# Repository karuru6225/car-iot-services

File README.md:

# car-iot-services

車載 IoT システム。ESP32-S3 が車載バッテリー電圧・電流・電力を計測し、
SORACOM Cat-M 経由で AWS IoT Core に送信する。
クラウド側では S3 + Athena でデータを蓄積し、CloudFront ホスティングの Web 管理画面でグラフ表示・削除操作を行える。

## システム構成

```text
ESP32-S3-MINI-1 (esp32_iot_gateway)
  ├── ADS1115 で 2 系統バッテリー電圧測定（サブ / メイン）
  ├── INA228 でサブバッテリー電流・電力・温度測定
  └── BLE スキャンで SwitchBot センサー（温湿度計 / CO2）受信
        ↓ MQTT over TLS
  SIM7080G (SORACOM Cat-M)
        ↓
  AWS IoT Core
  ├── Topic Rule → Lambda (ingest) → S3 (raw/year=.../month=.../day=.../hour=.../)
  │                                         ↓ Glue + Athena
  │                                   API Gateway → Lambda (query / delete)
  │                                         ↑ CloudFront → Web 管理画面 (index.html)
  ├── Shadow (desired/delta) → デバイス設定変更（充電制御・閾値等）
  └── IoT Jobs → OTA ファームウェア更新

  ※ 上記の LTE 経路とは別に、車内では BLE でスマートフォンと直接つながる
ESP32-S3-MINI-1 (esp32_iot_gateway)
        ↓ BLE (GATT Notify: 計測値・OBD-II)
  Android アプリ (car_iot_android)
    ├── Foreground Service で接続維持（アプリを閉じても受信継続）
    ├── Room に蓄積 → API Gateway へバッチアップロード（Cognito 認証）
    └── バッテリー / OBD / メーター表示・PiP
```

## ハードウェア

| 項目 | 内容 |
| ---- | ---- |
| MCU | ESP32-S3-MINI-1-N8（`m5atom_power_adc` 基板直付け） |
| ADC | ADS1115（I2C: SDA=GPIO17, SCL=GPIO18, ADDR=0x48） |
| 電流計 | INA228（I2C: SDA=GPIO17, SCL=GPIO18, ADDR=0x40） |
| OLED | SSD1306 128×64（I2C: SDA=GPIO17, SCL=GPIO18, ADDR=0x3C） |
| BLE | SwitchBot WoIOSensor（温湿度計）/ CO2センサー（アドバタイズ受信） |
| ボタン | GPIO26（Btn0）/ GPIO33（Btn1） |
| LTE | M5Stack U128（SIM7080G CAT-M/NB-IoT）、SORACOM SIM |
| 電源 | 車載 12V → LM2596（12V→5V）→ AMS1117-3.3（5V→3.3V）→ ESP32 |

## リポジトリ構成

```text
car-iot-services/
├── esp32_iot_gateway/     ESP32-S3-MINI-1 ゲートウェイ（アクティブ）
│   ├── ARCHITECTURE.md    レイヤー構成・依存ルール
│   ├── CONTEXT.md         実装詳細・設計決定・TODO
│   ├── OTA.md             OTA 仕様
│   ├── RELEASE.md         リリース手順（GitHub Actions）
│   └── MENU.md            OLED メニュー仕様
├── m5atom_iot_gateway/    M5Atom S3 ゲートウェイ（段階的廃止予定）
├── car_iot_android/       Android アプリ（Kotlin + Jetpack Compose、BLE 受信・アップロード）
│   └── CONTEXT.md         実装状態・実機検証メモ・UIデザインの設計判断
├── m5atom_power_adc/      新 PCB KiCad プロジェクト（電源・ADC・リレー・ESP32-S3 直付け）
│   ├── HARDWARE.md        ハードウェア設計仕様（BOM・回路・PCB レイアウト）
│   ├── CIRCUIT.md         回路設計仕様書
│   └── *.kicad_sch        階層シート構成（メイン + GroveUnit / RelayControl / VoltageSense）
├── infra/                 クラウドインフラ（Terraform）
│   ├── manage.ps1         デプロイスクリプト（plan / apply）
│   └── lambda_src/        Lambda ソースコード
│       └── TESTING.md     Lambdaユニットテストの実行方法（Docker + moto + pytest）
├── ops/                   運用スクリプト
│   ├── provision_device.ps1  ESP32 初回プロビジョニング（証明書発行・SPIFFS 書き込み）
│   ├── gen_certs.ps1      証明書生成
│   └── send_command.ps1   IoT Jobs コマンド送信
├── web/
│   ├── index.html         Web 管理画面（グラフ表示・データ削除）
│   └── admin.html         管理画面（デバイス一覧・Shadow 設定・充電制御）
├── docs/                  調査・設計メモ
├── tools/                 開発補助ツール（KiCad MCP サーバー等）
├── rtx830_filter_updater/ RTX830 フィルタ更新スクリプト
├── ARCHITECTURE.md
├── CONTEXT.md             開発引き継ぎ資料
└── SIM7080G.md            SIM7080G AT コマンドリファレンス
```

## デプロイ

### 前提

- Terraform >= 1.5
- AWS CLI（認証済み）
- 以下のファイルを `infra/` に配置（gitignore 済み）:
  - `backend.tfbackend` — S3 バックエンド設定
  - `terraform.tfvars` — 変数定義（`hosted_zone_id`, `web_subdomain` 等、`terraform.tfvars.example` を参照）

### インフラ + Lambda

`infra/` ディレクトリで PowerShell を実行:

```powershell
# 変更確認
.\manage.ps1 plan

# 適用（確認プロンプトあり）
.\manage.ps1 apply

# 確認なしで即適用
.\manage.ps1 apply -AutoApprove

# AWS プロファイルを指定する場合
.\manage.ps1 apply -Profile myprofile
```

Lambda コード（`lambda_src/`）の変更も `apply` で自動デプロイされる（`archive_file` の `source_code_hash` で変更検知）。

### Web 管理画面

`index.html` は `aws_s3_object` で Terraform 管理されているため、`manage.ps1 apply` で自動アップロードされる。
API エンドポイント・Cognito 設定はデプロイ時に Terraform が HTML 内のプレースホルダーを置換して埋め込む。

CloudFront のキャッシュ TTL はデフォルト 300 秒。URL は apply 後に確認できる:

```powershell
cd infra
terraform output web_url
```

## デバイスファームウェア

PlatformIO でビルド・書き込み。`esp32_iot_gateway/` を参照。

### 初回プロビジョニング

```powershell
cd ops
.\provision_device.ps1 -Port COM3
# AWS プロファイルを指定する場合
.\provision_device.ps1 -Port COM3 -Profile myprofile
# m5atom_power_adc v2 基板の場合（未指定時は v1 = 1）
.\provision_device.ps1 -Port COM3 -BoardVersion 2
```

スクリプトが MAC アドレスからデバイス ID（`esp32-gw-xxxxxxxxxxxx`）を生成し、AWS IoT Core に Thing を登録・証明書を発行・SPIFFS に書き込む。基板バージョンは NVS（`device/board_version`）にも書き込まれる。

同時に `-BoardVersion` に応じた Thing グループ（`ota-target-car-iot-gw-v1` または `-v2`）へも自動登録され、OTA の配信対象になる。グループに入っていないデバイスには OTA ジョブが届かない。

### OTA リリース

`vX.Y.Z` タグを push すると GitHub Actions が自動でビルド・S3 アップロード・IoT Job 作成・GitHub Release を実行する。MAJOR桁は基板シリーズ固定（1=v1基板、2=v2基板）。`src/config.h` の `FIRMWARE_VERSION_BASE` が正で、タグの数字と一致しないとビルドはエラーで停止する（先に `config.h` を更新してからタグを打つ）。

```powershell
git tag v1.2.3
git push origin main --tags
```

詳細は [esp32_iot_gateway/RELEASE.md](esp32_iot_gateway/RELEASE.md) および [esp32_iot_gateway/OTA.md](esp32_iot_gateway/OTA.md) を参照。

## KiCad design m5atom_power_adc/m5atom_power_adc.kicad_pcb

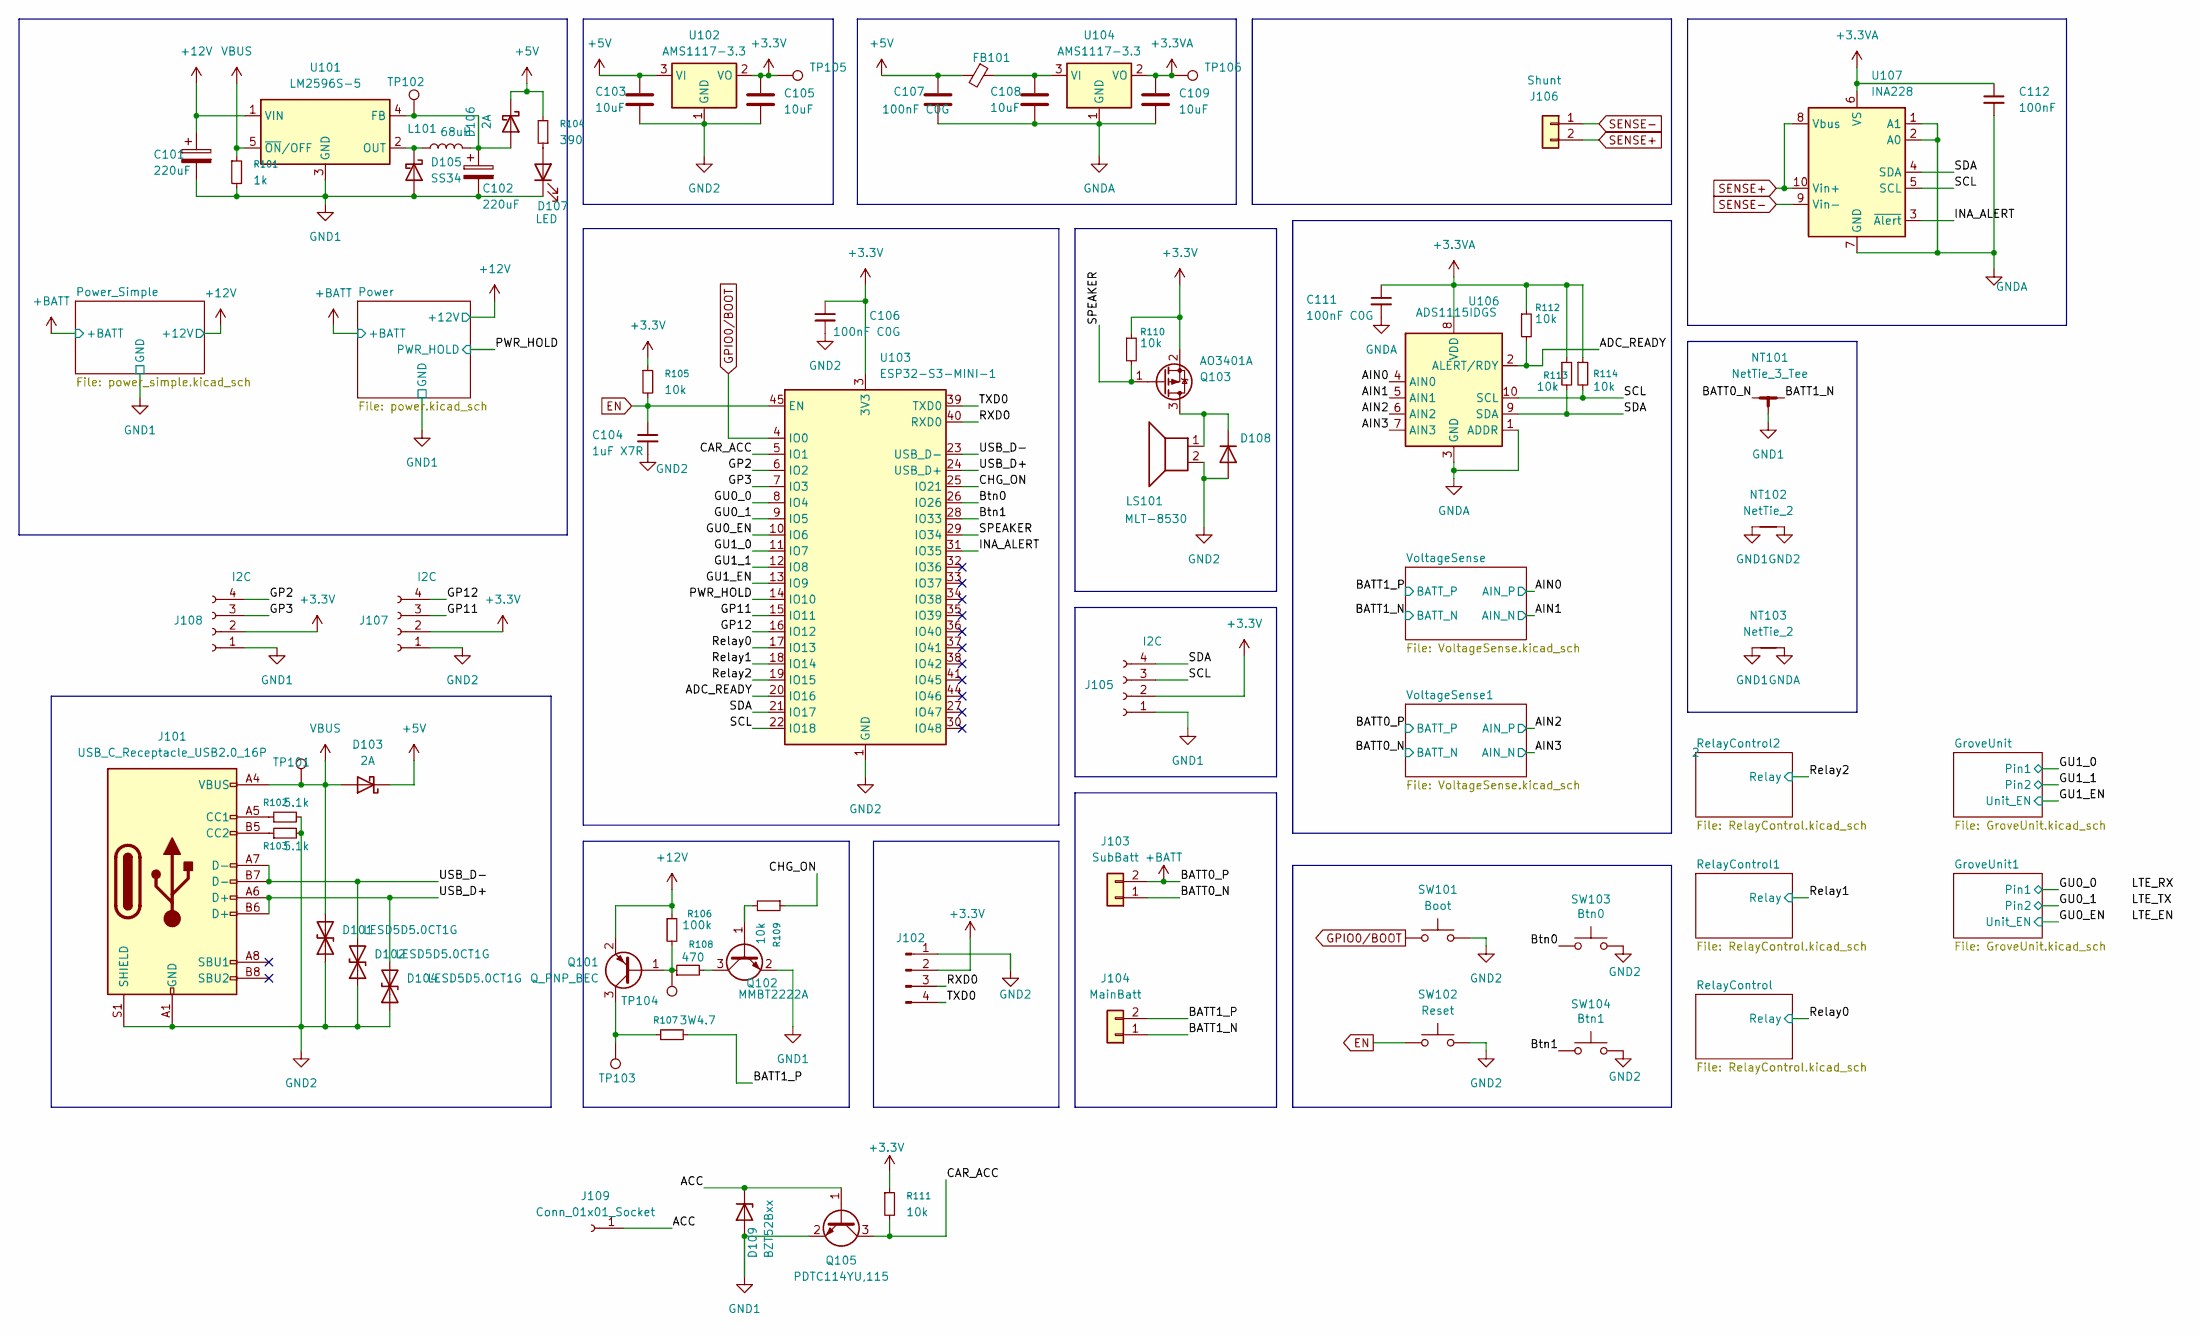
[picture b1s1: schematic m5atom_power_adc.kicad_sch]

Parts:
C101, C102: 220uF; CP_Elec_10x10; LCSC C125976
C103, C105, C108, C109: 10uF; C_0805_2012Metric; LCSC C32635
C104: 1uF X7R; C_0603_1608Metric; LCSC C5199872
C106, C107, C111: 100nF C0G; C_1206_3216Metric; LCSC C2168319
C112: 100nF; C_0603_1608Metric; LCSC C14663
D101, D102, D104: LESD5D5.0CT1G; D_SOD-523; LCSC C5199850
D103, D106: 2A; D_SOD-123F; LCSC C496544
D105: SS34; D_SMA; LCSC C8678
D107: LED; LED_0603_1608Metric; LCSC C965804
D108: 1N4148WS; D_SOD-323; LCSC C2128
D109: BZT52Bxx; D_SOD-123; LCSC C2932746
FB101: 500mA 600Ω@100MHz; L_0805_2012Metric; LCSC C1017
J101: USB_C_Receptacle_USB2.0_16P; USB_C_Receptacle_HRO_TYPE-C-31-M-12; LCSC C2765186
J102: Conn_01x04_Pin; PinHeader_1x04_P2.54mm_Vertical
J103: SubBatt; JST_XH_B2B-XH-A_1x02_P2.50mm_Vertical; LCSC C158012
J104: MainBatt; JST_XH_B2B-XH-A_1x02_P2.50mm_Vertical; LCSC C158012
J105: I2C; JST_XH_B4B-XH-A_1x04_P2.50mm_Vertical; LCSC C144395
J106: Shunt; JST_XH_B2B-XH-A_1x02_P2.50mm_Vertical; LCSC C158012
J107, J108: I2C; HY2.0-4PZZ; LCSC C144395
J109: Conn_01x01_Socket; PinHeader_1x01_P2.54mm_Vertical
L101: 68uH; PSPMAA0605H-680M-IGF; LCSC C2983094
LS101: MLT-8530; LCSC C94599
NT101: NetTie_3_Tee; NetTie-3_SMD_Pad2.0mm
NT102: NetTie_2; NetTie-2_SMD_Pad2.0mm
NT103: NetTie_2; NetTie-2_SMD_Pad0.5mm
Q101: Q_PNP_BEC; SOT-23; LCSC C7420371
Q102: MMBT2222A; SOT-23; LCSC C8512
Q103: AO3401A; SOT-23; LCSC C15127
Q105: PDTC114YU,115; SOT-323_SC-70; LCSC C80495
R101: 1k; R_0603_1608Metric; LCSC C21190
R102, R103: 5.1k; R_0603_1608Metric; LCSC C23186
R104: 390; R_0603_1608Metric; LCSC C23151
R105, R109, R110, R111, R112, R113, R114: 10k; R_0603_1608Metric; LCSC C25804
R106: 100k; R_0603_1608Metric; LCSC C25803
R107: 3W4.7; R_2512_6332Metric; LCSC C3924519
R108: 470; R_0603_1608Metric; LCSC C25803
SW101: Boot; SW_SPST_PTS810; LCSC C221897
SW102: Reset; SW_SPST_PTS810; LCSC C221897
SW103: Btn0; SW_SPST_PTS810; LCSC C221897
SW104: Btn1; SW_SPST_PTS810; LCSC C221897
TP101, TP102, TP103, TP104, TP105, TP106: TestPoint; TestPoint_Pad_D1.5mm
U101: LM2596S-5; TO-263-5_TabPin3; LCSC C5349985
U102, U104: AMS1117-3.3; SOT-223-3_TabPin2; LCSC C6186
U103: ESP32-S3-MINI-1; ESP32-S2-MINI-1; LCSC C2913206
U106: ADS1115IDGS; VSSOP-10_3x3mm_P0.5mm; LCSC C468683
U107: INA228; VSSOP-10_3x3mm_P0.5mm; LCSC C2887910

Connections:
+3.3V: C105.1, C106.1, J102.2, J105.2, J107.2, J108.2, Q103.2 (S), R105.1, R110.1, R111.1, TP105.1, U102.2 (VO), U103.3 (3V3)
+3.3VA: C109.1, C111.1, C112.1, R112.1, R113.1, R114.1, TP106.1, U104.2 (VO), U106.8 (VDD), U107.6 (VS)
+5V: C103.1, C107.1, D103.1 (K), D106.1 (K), FB101.2, R104.2, U102.3 (VI); also elsewhere on the board
+12V: C101.1, Q101.2 (E), R106.1, U101.1 (VIN); also elsewhere on the board
+BATT: J103.2; also elsewhere on the board
/ACC: D109.1 (K), J109.1, Q105.1 (B)
/ADC_READY: R112.2, U103.20 (IO16), U106.2 (ALERT/RDY)
/AIN0: U106.4 (AIN0); also elsewhere on the board
/AIN1: U106.5 (AIN1); also elsewhere on the board
/AIN2: U106.6 (AIN2); also elsewhere on the board
/AIN3: U106.7 (AIN3); also elsewhere on the board
/BATT0_N: J103.1, NT101.1; also elsewhere on the board
/BATT1_N: J104.1, NT101.2; also elsewhere on the board
/BATT1_P: J104.2, R107.2; also elsewhere on the board
/Btn0: SW103.1, U103.26 (IO26)
/Btn1: SW104.1, U103.28 (IO33)
/CAR_ACC: Q105.3 (C), R111.2, U103.5 (IO1)
/CHG_ON: R109.1, U103.25 (IO21)
/GP2: J108.4, U103.6 (IO2)
/GP3: J108.3, U103.7 (IO3)
/GP11: J107.3, U103.15 (IO11)
/GP12: J107.4, U103.16 (IO12)
/GU0_0: U103.8 (IO4); also elsewhere on the board
/GU0_1: U103.9 (IO5); also elsewhere on the board
/GU0_EN: U103.10 (IO6); also elsewhere on the board
/GU1_EN: U103.13 (IO9); also elsewhere on the board
/INA_ALERT: U103.31 (IO35), U107.3 (~Alert)
/PWR_HOLD: U103.14 (IO10); also elsewhere on the board
/RXD0: J102.3, U103.40 (RXD0)
/Relay0: U103.17 (IO13); also elsewhere on the board
/Relay1: U103.18 (IO14); also elsewhere on the board
/Relay2: U103.19 (IO15); also elsewhere on the board
/SCL: J105.3, R114.2, U103.22 (IO18), U106.10 (SCL), U107.5 (SCL)
/SDA: J105.4, R113.2, U103.21 (IO17), U106.9 (SDA), U107.4 (SDA)
/SPEAKER: Q103.1 (G), R110.2, U103.29 (IO34)
/TXD0: J102.4, U103.39 (TXD0)
/USB_D+: D104.2 (A2), J101.A6 (D+), J101.B6 (D+), U103.24 (USB_D+)
/USB_D-: D102.2 (A2), J101.A7 (D-), J101.B7 (D-), U103.23 (USB_D-)
EN: C104.1, R105.2, SW102.1, U103.45 (EN)
GND2: C103.2, C104.2, C105.2, C106.2, D101.1 (A1), D102.1 (A1), D104.1 (A1), D108.2 (A), J101.A1 (GND), J101.A12 (GND), J101.B1 (GND), J101.B12 (GND), J101.S1 (SHIELD), J102.1, J107.1, LS101.2, NT102.2, R102.2, R103.2, SW101.2, SW102.2, SW103.2, SW104.2, U102.1 (GND), U103.1 (GND), U103.2 (GND), U103.42 (GND), U103.43 (GND), U103.46 (GND), U103.47 (GND), U103.48 (GND), U103.49 (GND), U103.50 (GND), U103.51 (GND), U103.52 (GND), U103.53 (GND), U103.54 (GND), U103.55 (GND), U103.56 (GND), U103.57 (GND), U103.58 (GND), U103.59 (GND), U103.60 (GND), U103.61 (GND), U103.62 (GND), U103.63 (GND), U103.64 (GND), U103.65 (GND)
GNDA: C107.2, C108.2, C109.2, C111.2, C112.2, NT103.2, U104.1 (GND), U106.1 (ADDR), U106.3 (GND), U107.1 (A1), U107.2 (A0), U107.7 (GND); also elsewhere on the board
GPIO0/BOOT: SW101.1, U103.4 (IO0)
unnamed: D105.1 (K), L101.1, U101.2 (OUT)
unnamed: C102.1, D106.2 (A), L101.2, TP102.1, U101.4 (FB)
unnamed: D107.2 (A), R104.1
unnamed: D108.1 (K), LS101.1, Q103.3 (D)
unnamed: J101.A5 (CC1), R102.1
unnamed: J101.B5 (CC2), R103.1
unnamed: Q101.1 (B), R106.2, R108.1, TP104.1
unnamed: Q101.3 (C), R107.1, TP103.1
unnamed: Q102.1 (B), R109.2
unnamed: Q102.3 (C), R108.2
unnamed: C108.1, FB101.1, U104.3 (VI)
SENSE+: J106.2, U107.8 (Vbus), U107.10 (Vin+)
SENSE-: J106.1, U107.9 (Vin-)
VBUS: D101.2 (A2), D103.2 (A), J101.A4 (VBUS), J101.A9 (VBUS), J101.B4 (VBUS), J101.B9 (VBUS), R101.1, TP101.1, U101.5 (~ON/OFF)

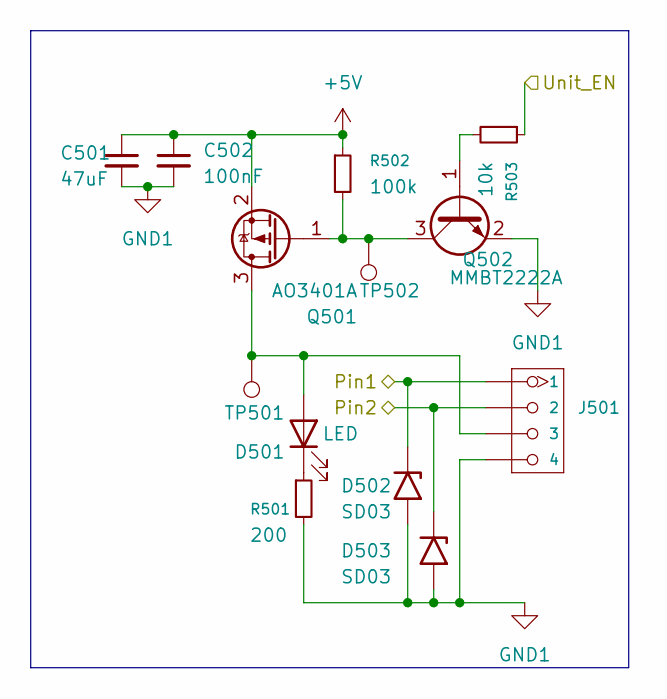
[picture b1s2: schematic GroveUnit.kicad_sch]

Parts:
C501: 47uF; C_1206_3216Metric; LCSC C22367835
C502: 100nF; C_0603_1608Metric; LCSC C14663
D501: LED; LED_0603_1608Metric; LCSC C965804
D502, D503: SD03; D_SOD-323; LCSC C502526
J501: GROVE-CONNECTOR; HY2.0-4PZZ; LCSC C7429580
Q501: AO3401A; SOT-23; LCSC C15127
Q502: MMBT2222A; SOT-23; LCSC C8512
R501: 200; R_0603_1608Metric; LCSC C8218
R502: 100k; R_0603_1608Metric; LCSC C2906981
R503: 10k; R_0402_1005Metric; LCSC C2906862
TP501, TP502: TestPoint; TestPoint_Pad_D1.5mm

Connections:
+5V: C501.1, C502.1, Q501.2 (S), R502.1; also elsewhere on the board
/GU1_EN: R503.1; also elsewhere on the board
unnamed: D501.1 (K), R501.1
unnamed: Q501.1 (G), Q502.3 (C), R502.2, TP502.1
unnamed: Q502.1 (B), R503.2

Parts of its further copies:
C601: 47uF; C_1206_3216Metric; LCSC C22367835
C602: 100nF; C_0603_1608Metric; LCSC C14663
D601: LED; LED_0603_1608Metric; LCSC C965804
D602, D603: SD03; D_SOD-323; LCSC C502526
J601: GROVE-CONNECTOR; HY2.0-4PZZ; LCSC C7429580
Q601: AO3401A; SOT-23; LCSC C15127
Q602: MMBT2222A; SOT-23; LCSC C8512
R602: 100k; R_0603_1608Metric; LCSC C2906981
R603: 10k; R_0402_1005Metric; LCSC C2906862
TP601, TP602: TestPoint; TestPoint_Pad_D1.5mm

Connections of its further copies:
+5V: C601.1, C602.1, Q601.2 (S), R602.1; also elsewhere on the board
/GU0_0: D602.1 (A1), J601.4; also elsewhere on the board
/GU0_1: D603.1 (A1), J601.3; also elsewhere on the board
/GU0_EN: R603.1; also elsewhere on the board
unnamed: D601.2 (A), J601.2, Q601.3 (D), TP601.1
unnamed 56: D601.1 (K); also elsewhere on the board
unnamed: Q601.1 (G), Q602.3 (C), R602.2, TP602.1
unnamed: Q602.1 (B), R603.2

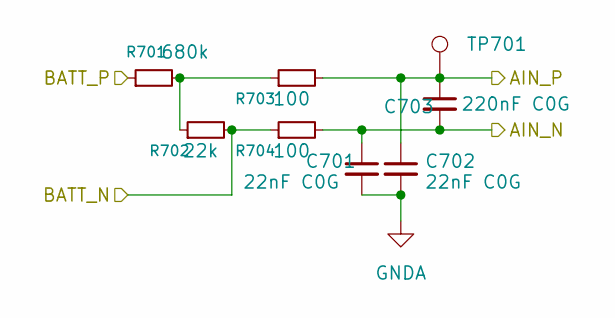
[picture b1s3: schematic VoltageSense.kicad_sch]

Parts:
C701, C702: 22nF C0G; C_0805_2012Metric; LCSC C77069
C703: 220nF C0G; C_1206_3216Metric; LCSC C464977
R701: 680k; R_0603_1608Metric; LCSC C2989042
R702: 22k; R_0402_1005Metric; LCSC C326601
R703, R704: 100; R_0402_1005Metric; LCSC C705627
TP701: TestPoint; TestPoint_Pad_D1.5mm

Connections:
/AIN0: C702.1, C703.1, R703.2, TP701.1; also elsewhere on the board
/AIN1: C701.1, C703.2, R704.2; also elsewhere on the board
/BATT1_N: R702.2, R704.1; also elsewhere on the board
/BATT1_P: R701.1; also elsewhere on the board
GNDA: C701.2, C702.2; also elsewhere on the board
unnamed: R701.2, R702.1, R703.1

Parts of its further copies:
C801, C802: 22nF C0G; C_0805_2012Metric; LCSC C77069
C803: 220nF C0G; C_1206_3216Metric; LCSC C464977
R801: 680k; R_0603_1608Metric; LCSC C2989042
R802: 22k; R_0402_1005Metric; LCSC C326601
R803, R804: 100; R_0402_1005Metric; LCSC C705627
TP801: TestPoint; TestPoint_Pad_D1.5mm

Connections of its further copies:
+BATT: R801.1; also elsewhere on the board
/AIN2: C802.1, C803.1, R803.2, TP801.1; also elsewhere on the board
/AIN3: C801.1, C803.2, R804.2; also elsewhere on the board
/BATT0_N: R802.2, R804.1; also elsewhere on the board
GNDA: C801.2, C802.2; also elsewhere on the board
unnamed: R801.2, R802.1, R803.1

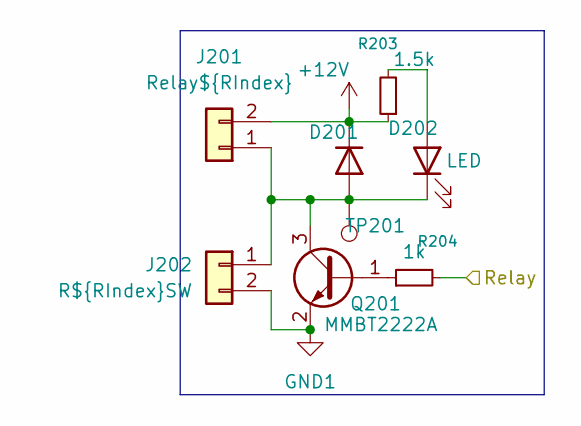
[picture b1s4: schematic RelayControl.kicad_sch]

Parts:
D201: 1N4148WS; D_SOD-323; LCSC C2128
D202: LED; LED_0603_1608Metric; LCSC C965799
J201: Relay${RIndex}; JST_XH_B2B-XH-A_1x02_P2.50mm_Vertical; LCSC C158012
J202: R${RIndex}SW; JST_XH_B2B-XH-A_1x02_P2.50mm_Vertical; LCSC C158012
Q201: MMBT2222A; SOT-23; LCSC C8512
R203: 1.5k; R_1206_3216Metric; LCSC C114929
R204: 1k; R_0603_1608Metric; LCSC C21190
TP201: TestPoint; TestPoint_Pad_D1.5mm

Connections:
+12V: D201.1 (K), J201.2, R203.1; also elsewhere on the board
/Relay0: R204.2; also elsewhere on the board
unnamed: D201.2 (A), D202.1 (K), J201.1, J202.1, Q201.3 (C), TP201.1
unnamed: D202.2 (A), R203.2
unnamed: Q201.1 (B), R204.1

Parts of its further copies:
D301, D401: 1N4148WS; D_SOD-323; LCSC C2128
D302, D402: LED; LED_0603_1608Metric; LCSC C965799
Q301, Q401: MMBT2222A; SOT-23; LCSC C8512
R303, R403: 1.5k; R_1206_3216Metric; LCSC C114929
R304, R404: 1k; R_0603_1608Metric; LCSC C21190
TP301, TP401: TestPoint; TestPoint_Pad_D1.5mm

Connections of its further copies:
+12V: D301.1 (K), D401.1 (K), R303.1, R403.1; also elsewhere on the board
/Relay1: R304.2; also elsewhere on the board
/Relay2: R404.2; also elsewhere on the board
unnamed 50: D301.2 (A), D302.1 (K), Q301.3 (C), TP301.1; also elsewhere on the board
unnamed: D302.2 (A), R303.2
unnamed 52: D401.2 (A), D402.1 (K), Q401.3 (C), TP401.1; also elsewhere on the board
unnamed: D402.2 (A), R403.2
unnamed: Q301.1 (B), R304.1
unnamed: Q401.1 (B), R404.1

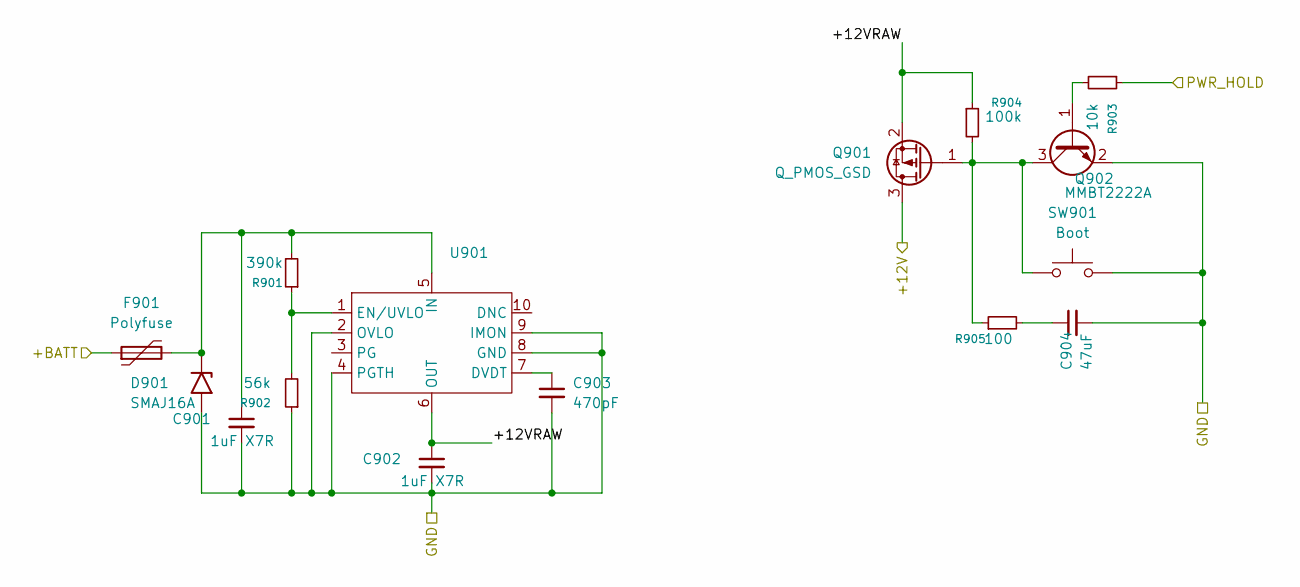
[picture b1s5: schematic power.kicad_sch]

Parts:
C901, C902: 1uF X7R; C_0603_1608Metric; LCSC C5199872
C903: 470pF; C_0603_1608Metric; LCSC C1620
C904: 47uF; C_1206_3216Metric; LCSC C22367835
D901: SMAJ16A; D_SMB; LCSC C19077571
F901: Polyfuse; Fuse_1812_4532Metric; LCSC C18198333
Q901: Q_PMOS_GSD; SOT-23; LCSC C52437601
Q902: MMBT2222A; SOT-23; LCSC C8512
R901: 390k; R_0603_1608Metric; LCSC C21190
R902: 56k; R_0603_1608Metric; LCSC C21190
R903: 10k; R_0603_1608Metric; LCSC C25804
R904: 100k; R_0603_1608Metric; LCSC C25803
R905: 100; R_0402_1005Metric; LCSC C705627
SW901: Boot; SW_SPST_PTS810; LCSC C221897
U901: VQFN-10-HR(2x2); LCSC C3210761

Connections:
+12V: Q901.3 (D); also elsewhere on the board
+BATT: F901.1; also elsewhere on the board
/PWR_HOLD: R903.1; also elsewhere on the board
/Power/+12VRAW: C902.1, Q901.2 (S), R904.1, U901.6 (OUT)
unnamed: C904.1, R905.2
unnamed: C901.1, D901.1 (A1), F901.2, R901.2, U901.5 (IN)
unnamed: Q901.1 (G), Q902.3 (C), R904.2, R905.1, SW901.1
unnamed: Q902.1 (B), R903.2
unnamed: C903.1, U901.7 (DVDT)
unnamed: R901.1, R902.2, U901.1 (EN/UVLO)

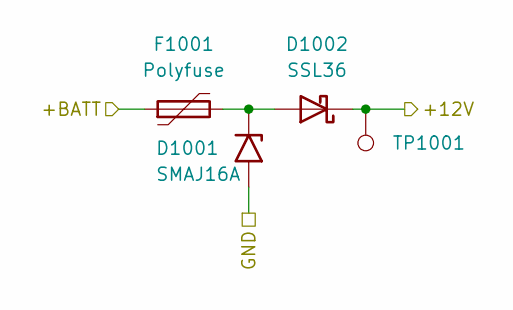
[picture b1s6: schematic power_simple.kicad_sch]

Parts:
D1001: SMAJ16A; D_SMB; LCSC C19077571
D1002: SSL36; D_SMA; LCSC C28646286
F1001: Polyfuse; Fuse_1812_4532Metric; LCSC C18198333
TP1001: TestPoint; TestPoint_Pad_D1.5mm

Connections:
unnamed: D1001.1 (A1), D1002.2 (A), F1001.2
unnamed: D1002.1 (K), TP1001.1

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
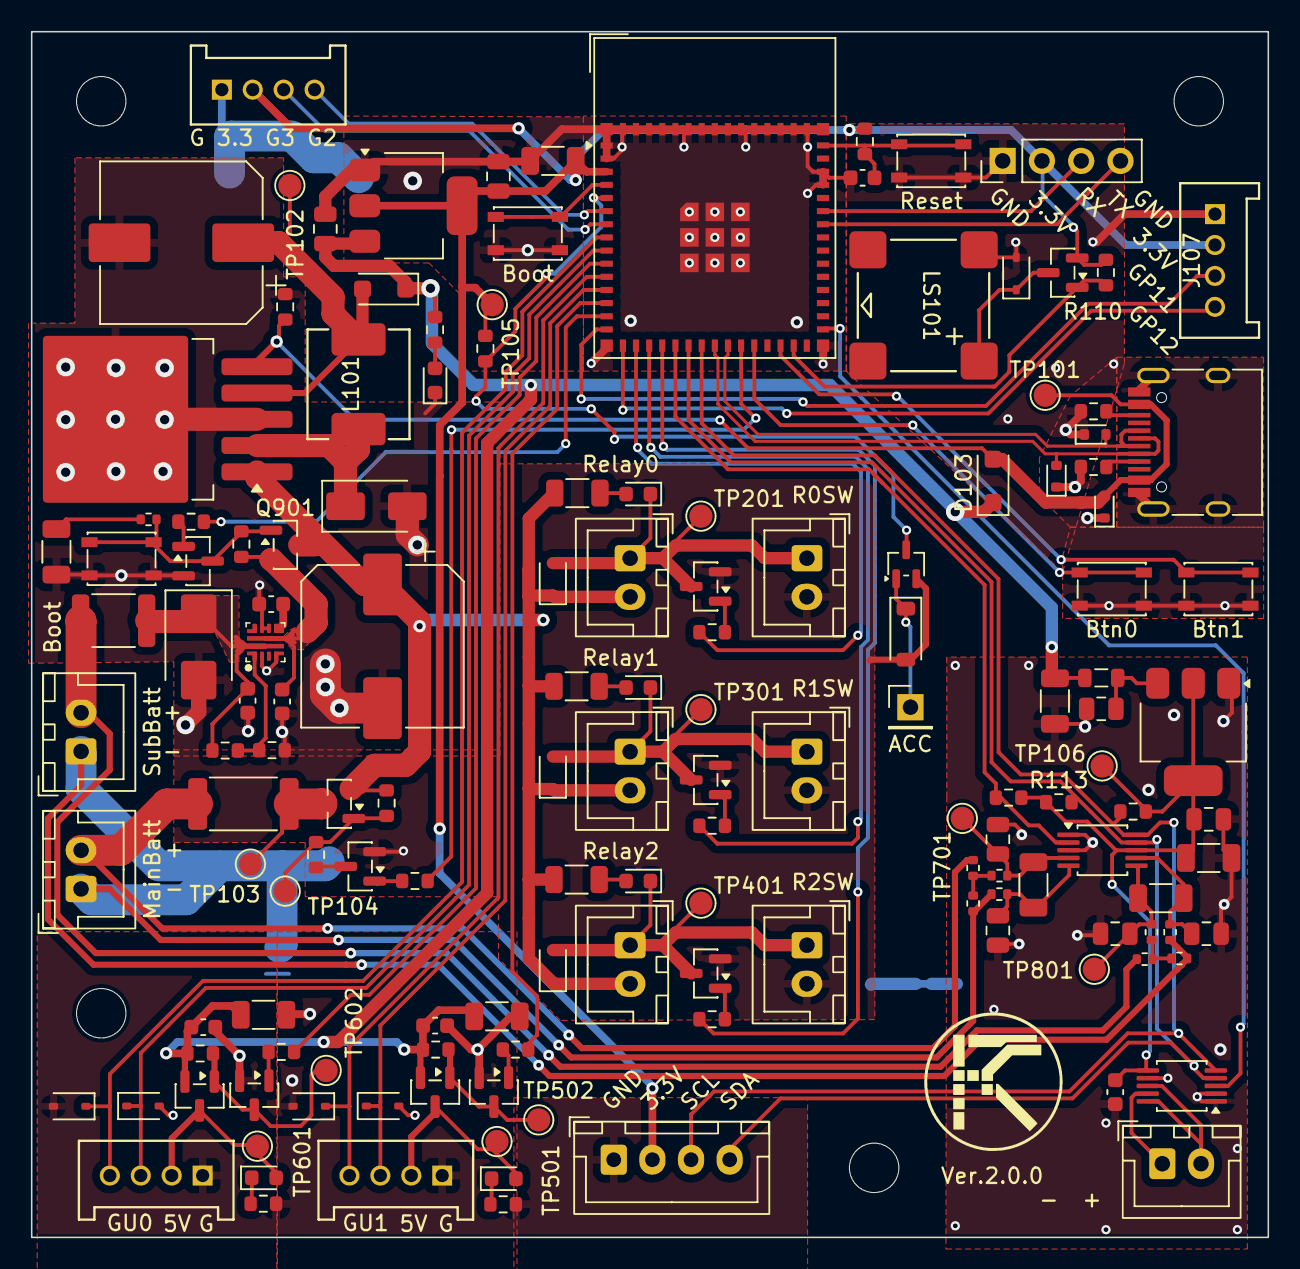
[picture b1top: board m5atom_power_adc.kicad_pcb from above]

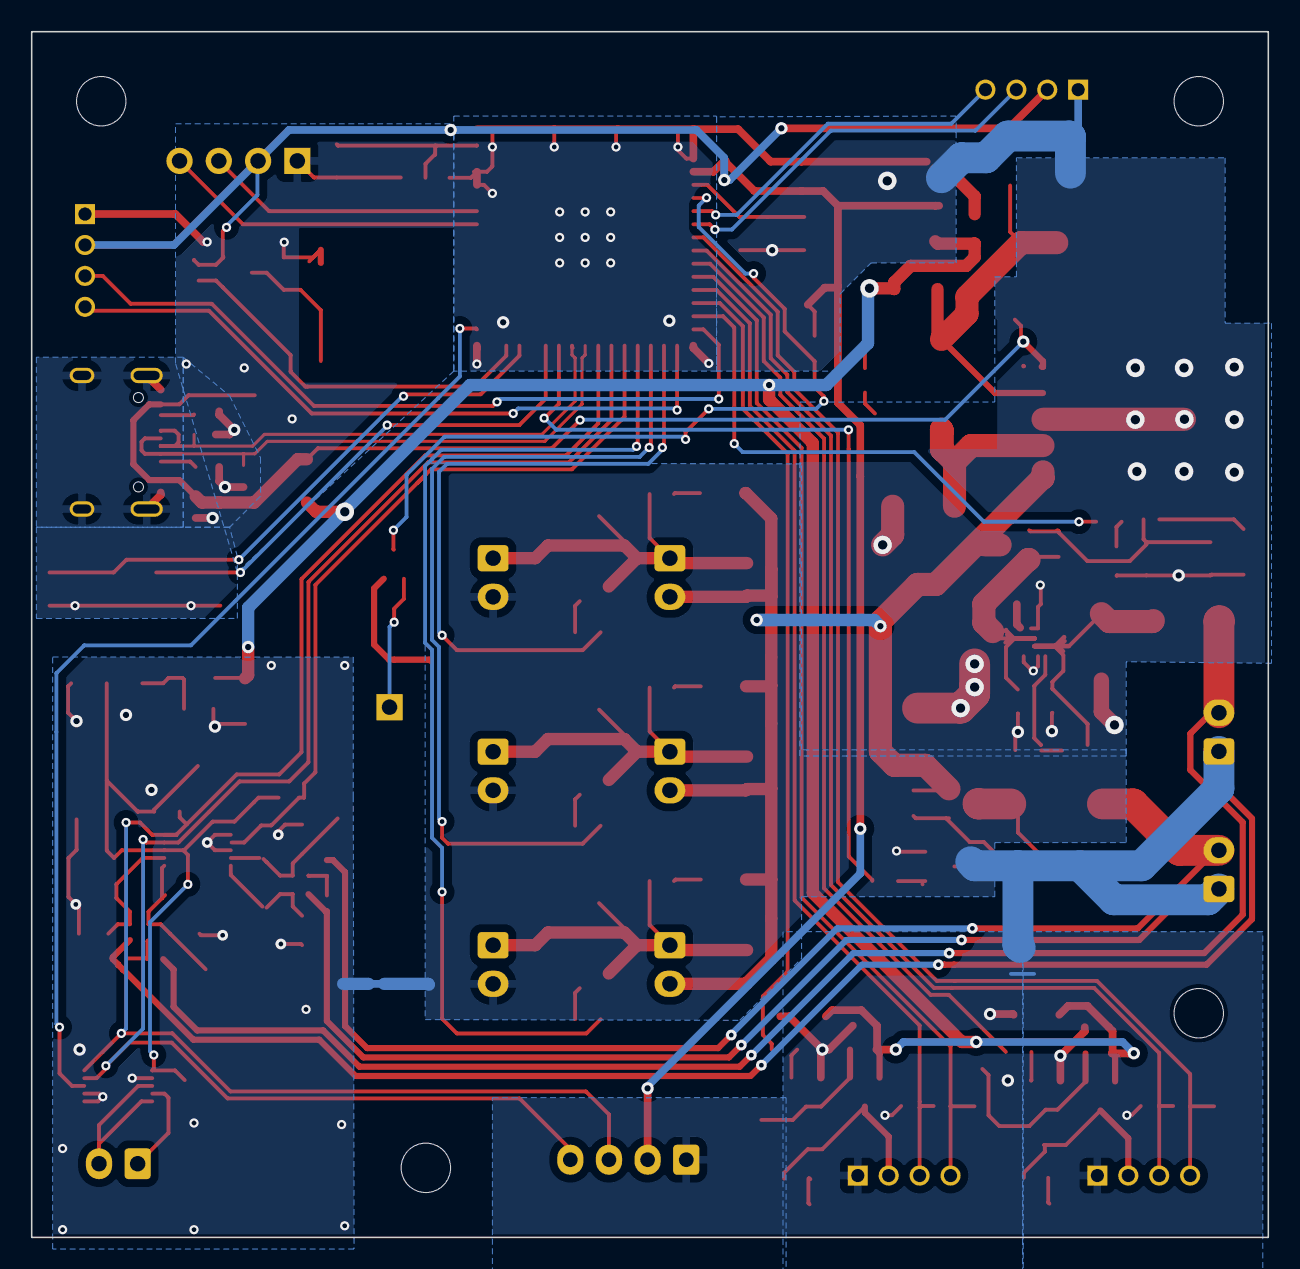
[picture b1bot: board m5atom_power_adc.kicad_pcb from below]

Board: 2 copper layers, 80.0 x 78.0 mm, 150 parts (3 on the bottom side), 85 nets.

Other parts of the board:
J301: Relay1; JST_XH_B2B-XH-A_1x02_P2.50mm_Vertical
J302: R1SW; JST_XH_B2B-XH-A_1x02_P2.50mm_Vertical
J401: Relay2; JST_XH_B2B-XH-A_1x02_P2.50mm_Vertical
J402: R2SW; JST_XH_B2B-XH-A_1x02_P2.50mm_Vertical
R601: 390; R_0603_1608Metric

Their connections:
+12V: J301.2, J401.2; also elsewhere on the board
unnamed 50: J301.1, J302.1; also elsewhere on the board
unnamed 52: J401.1, J402.1; also elsewhere on the board
unnamed 56: R601.1; also elsewhere on the board
